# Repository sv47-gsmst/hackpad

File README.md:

# Macropad

## <ins> Overview </ins>

I built a custom 6-key macropad with a rotary knob, designing the electronics, PCB, and case myself. The entire project took about 8 hours to finish, from the schematic to the case 

## Goal:

I wanted to create a compact mini keyboard that can help me with shortcuts and quick commands such as arrow keys. 

## Build Process:

This project involved wiring a schematic and PCB around a Seeeduino-XIAO microcontroller. As well as building a case for my PCB, and writing firmware for the macropad. Throughout this project I had many challenges in routing the wires in the schematic to the microcontroller, getting the right measurements and extruding the case properly, as well as checking to see if the PCB size and case size both fit perfectly. In the end the final product had a Schematic and PCB design, KMK firmware for the macropad, finished with a custom case.

### <ins> BOM </ins>

- 6x [Sw_Push : Cherry MX switches](https://mechanicalkeyboards.com/products/cherry-mx-red-45g-linear?variant=47357318922540)

+ 6x [1N4148 DO-35 Diodes](https://www.digikey.com/en/products/detail/onsemi/1N4148/458603?msockid=0ea5a3721be567da03c4b1871a33668c)

* 1x [EC11 RotaryEncoder_Switch](https://easyelecmodule.com/product/ec11-rotary-encoder-module/)

- 1x [RP2040 MOUDLE-SEEEDUINO-XIAO](https://wiki.seeedstudio.com/XIAO-RP2040/)

* 4x [M3x16mm screws](https://www.homedepot.com/p/Hillman-M6-1-00-x-10-mm-Internal-Hex-Button-Head-Cap-Screws-6-Pack-44478/204786183)

- 6x [Key Caps](https://www.amazon.com/PATIKIL-Universal-Replacement-Accessories-Mechanical/dp/B0B5KZQ9X9/ref=sxin_18_pa_sp_search_thematic_sspa?content-id=amzn1.sym.8eb671a2-a903-4c3a-b962-ebb867a4f8f8%3Aamzn1.sym.8eb671a2-a903-4c3a-b962-ebb867a4f8f8&crid=3QH7IDOZMB9E2&cv_ct_cx=blank%2Bpbt%2Bkeycaps%2B6&keywords=blank%2Bpbt%2Bkeycaps%2B6&pd_rd_i=B0B5KZQ9X9&pd_rd_r=f939268c-f093-490f-b81d-6251cd200ec7&pd_rd_w=dOYTZ&pd_rd_wg=8koAN&pf_rd_p=8eb671a2-a903-4c3a-b962-ebb867a4f8f8&pf_rd_r=KJT8BBVFVP47XRY7E2BV&qid=1787698632&sbo=RZvfv%2F%2FHxDF%2BO5021pAnSA%3D%3D&sprefix=blank%2Bpbt%2Bkeycaps%2B6%2Caps%2C152&sr=1-3-6024b2a3-78e4-4fed-8fed-e1613be3bcce-spons&aref=QON3oW3Zzx&sp_csd=d2lkZ2V0TmFtZT1zcF9zZWFyY2hfdGhlbWF0aWM&th=1)

+ 4x [M3 headsets](https://partsbuilt.com/m3-heat-set-thread-insert-5mm-long-4-pack/?utm_source=chatgpt.com)

### <ins> Software: </ins> 

- Kicad 10.0 for Schematic

+ Kicad 10.0 PCB design

* KMK firmware

- Autodesk Fusion 360 for CAD

##                                                               Screenshots

| PCB | Schematic | CAD |
|-----|-----------|-----|
||  |  |

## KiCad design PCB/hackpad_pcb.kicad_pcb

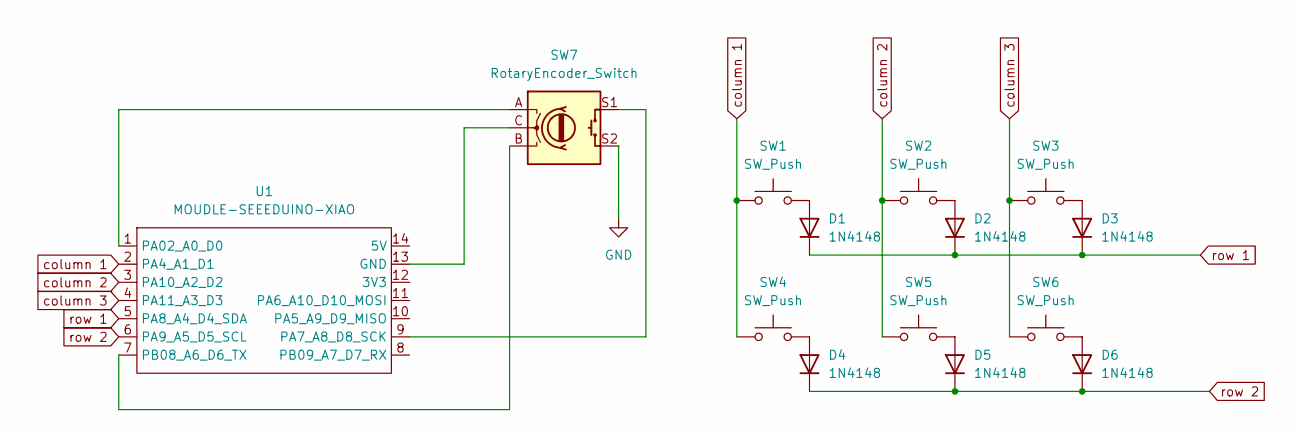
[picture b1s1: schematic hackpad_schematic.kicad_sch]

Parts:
D1, D2, D3, D4, D5, D6: 1N4148; D_DO-35_SOD27_P7.62mm_Horizontal
SW1, SW2, SW3, SW4, SW5, SW6: SW_Push; SW_Cherry_MX_1.00u_PCB
SW7: RotaryEncoder_Switch; RotaryEncoder_Alps_EC11E-Switch_Vertical_H20mm
U1: MOUDLE-SEEEDUINO-XIAO; XIAO-Generic-Hybrid-14P-2.54-21X17.8MM

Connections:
GND: SW7.S2
unnamed: D1.2 (A), SW1.2
unnamed: D2.2 (A), SW2.2
unnamed: D3.2 (A), SW3.2
unnamed: D4.2 (A), SW4.2
unnamed: D5.2 (A), SW5.2
unnamed: D6.2 (A), SW6.2
unnamed: SW7.C, U1.13 (GND)
unnamed: SW7.A, U1.1 (PA02_A0_D0)
unnamed: SW7.S1, U1.9 (PA7_A8_D8_SCK)
unnamed: SW7.B, U1.7 (PB08_A6_D6_TX)
column 1: SW1.1, SW4.1, U1.2 (PA4_A1_D1)
column 2: SW2.1, SW5.1, U1.3 (PA10_A2_D2)
column 3: SW3.1, SW6.1, U1.4 (PA11_A3_D3)
row 1: D1.1 (K), D2.1 (K), D3.1 (K), U1.5 (PA8_A4_D4_SDA)
row 2: D4.1 (K), D5.1 (K), D6.1 (K), U1.6 (PA9_A5_D5_SCL)

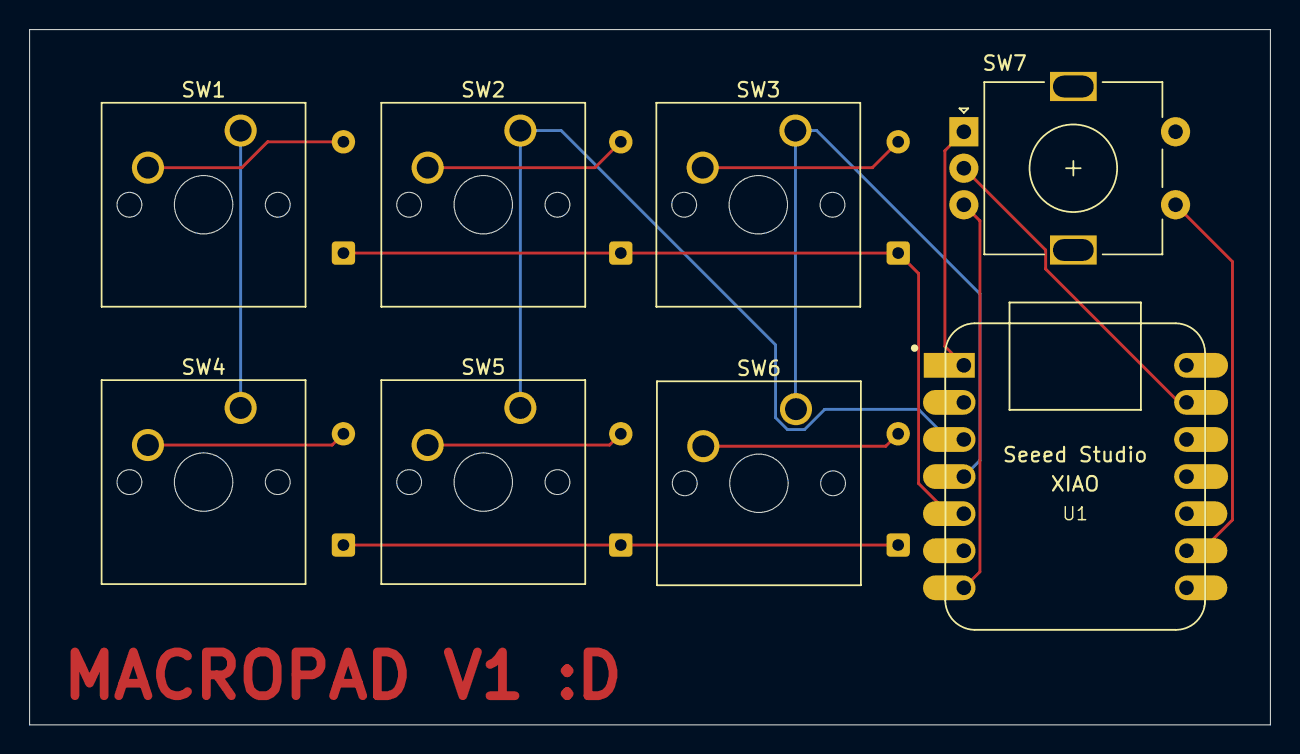
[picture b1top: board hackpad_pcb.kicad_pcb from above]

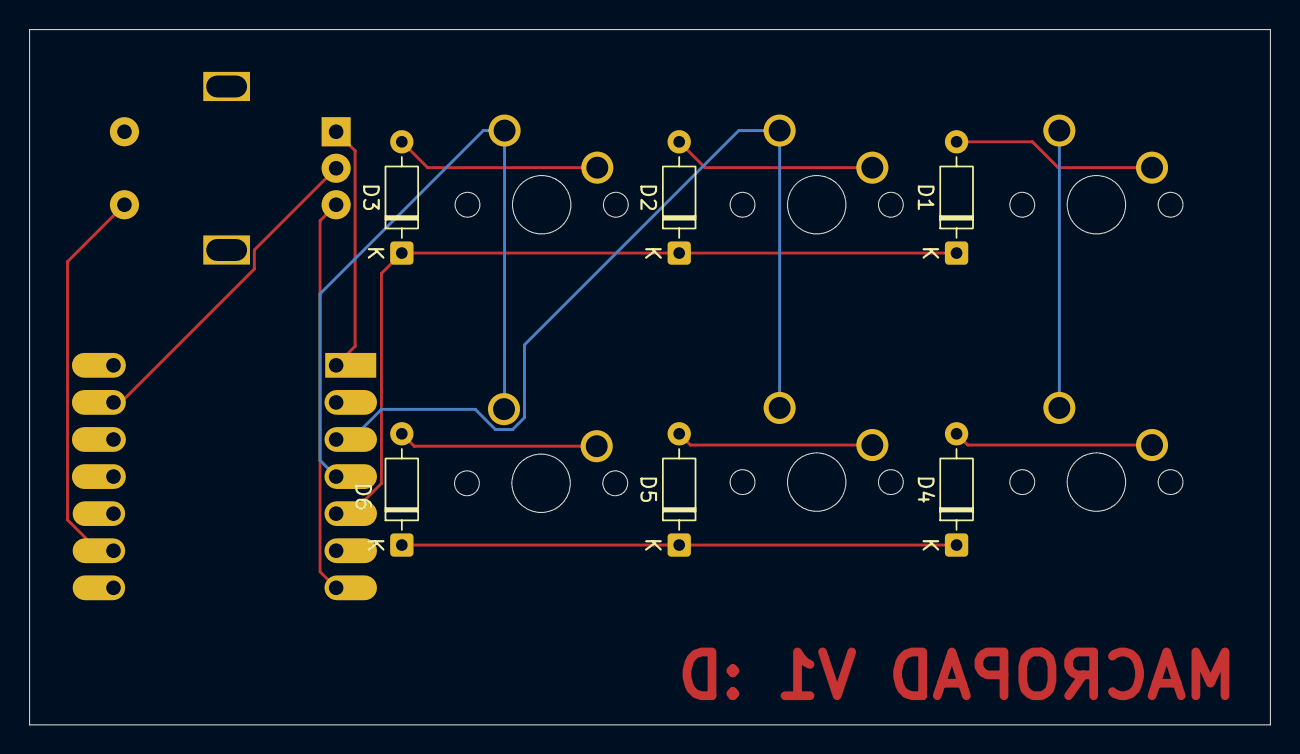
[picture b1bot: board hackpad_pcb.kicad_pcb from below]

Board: 2 copper layers, 85.0 x 47.6 mm, 14 parts (6 on the bottom side), 15 nets.
